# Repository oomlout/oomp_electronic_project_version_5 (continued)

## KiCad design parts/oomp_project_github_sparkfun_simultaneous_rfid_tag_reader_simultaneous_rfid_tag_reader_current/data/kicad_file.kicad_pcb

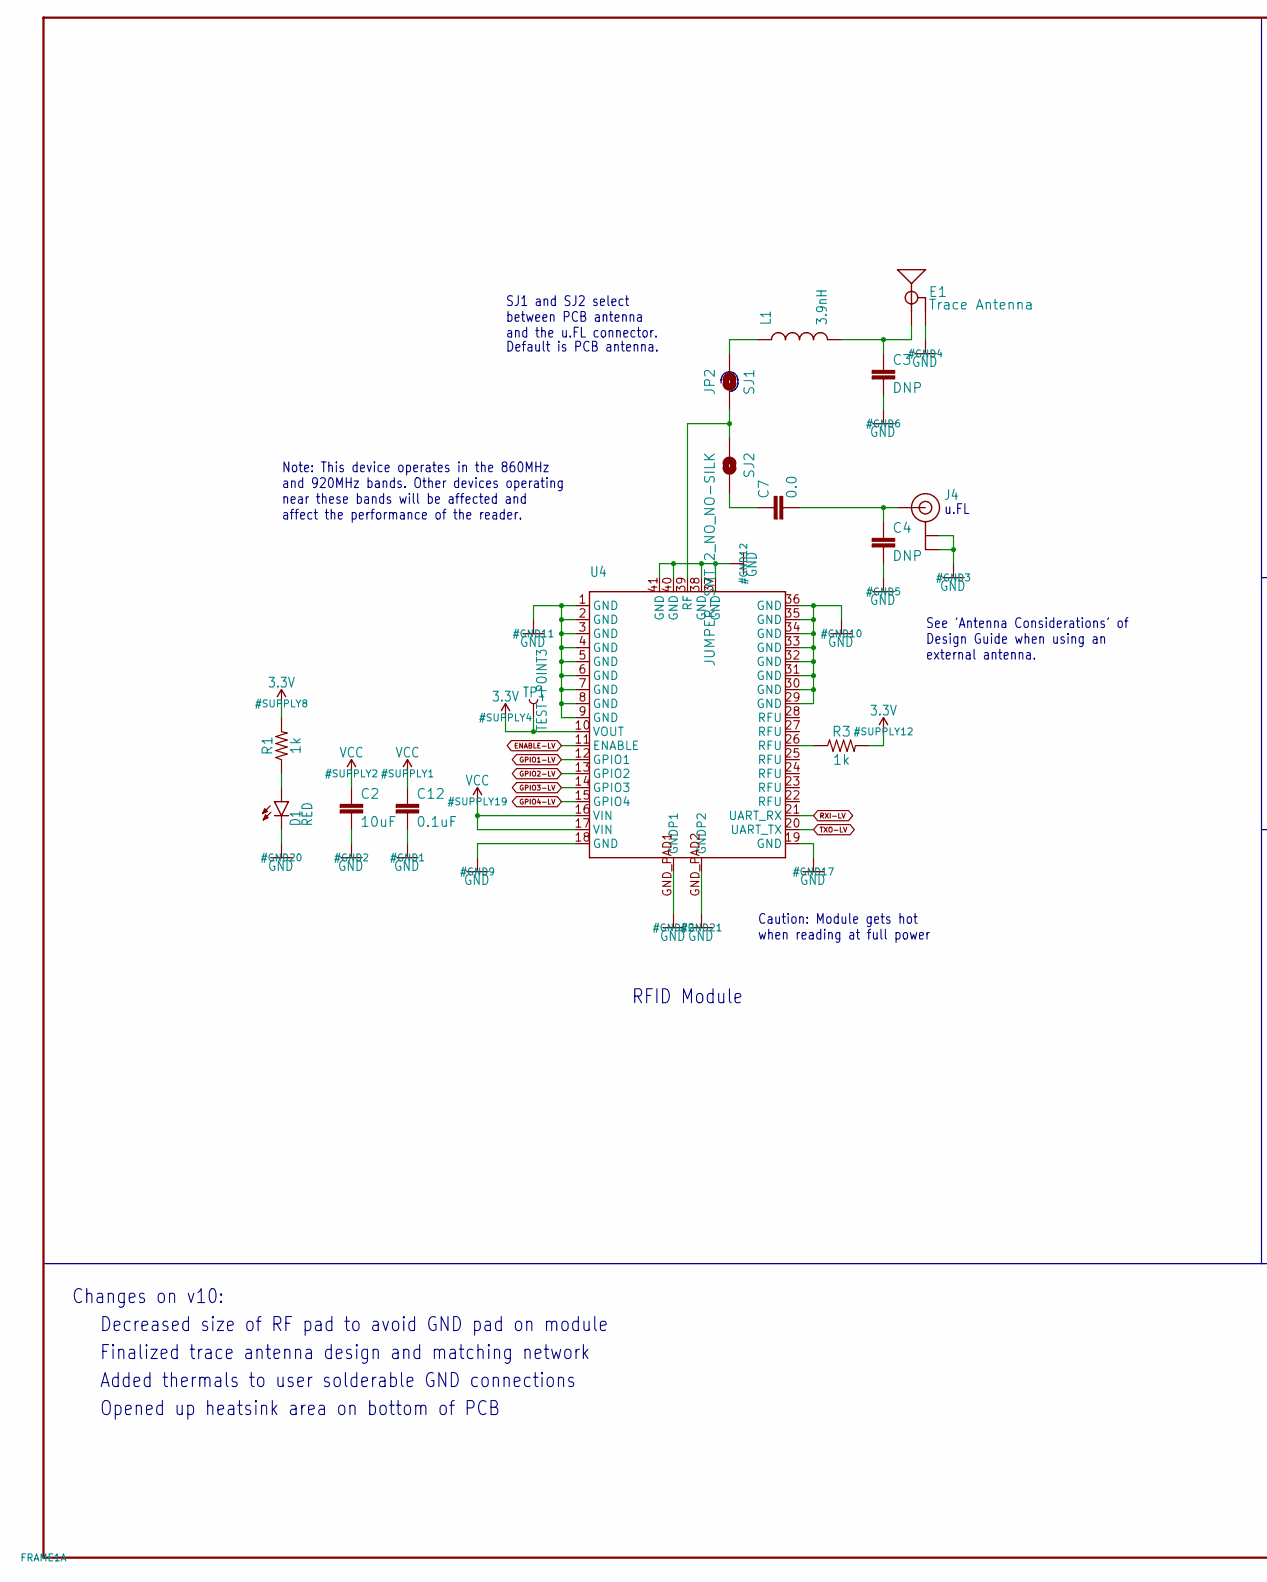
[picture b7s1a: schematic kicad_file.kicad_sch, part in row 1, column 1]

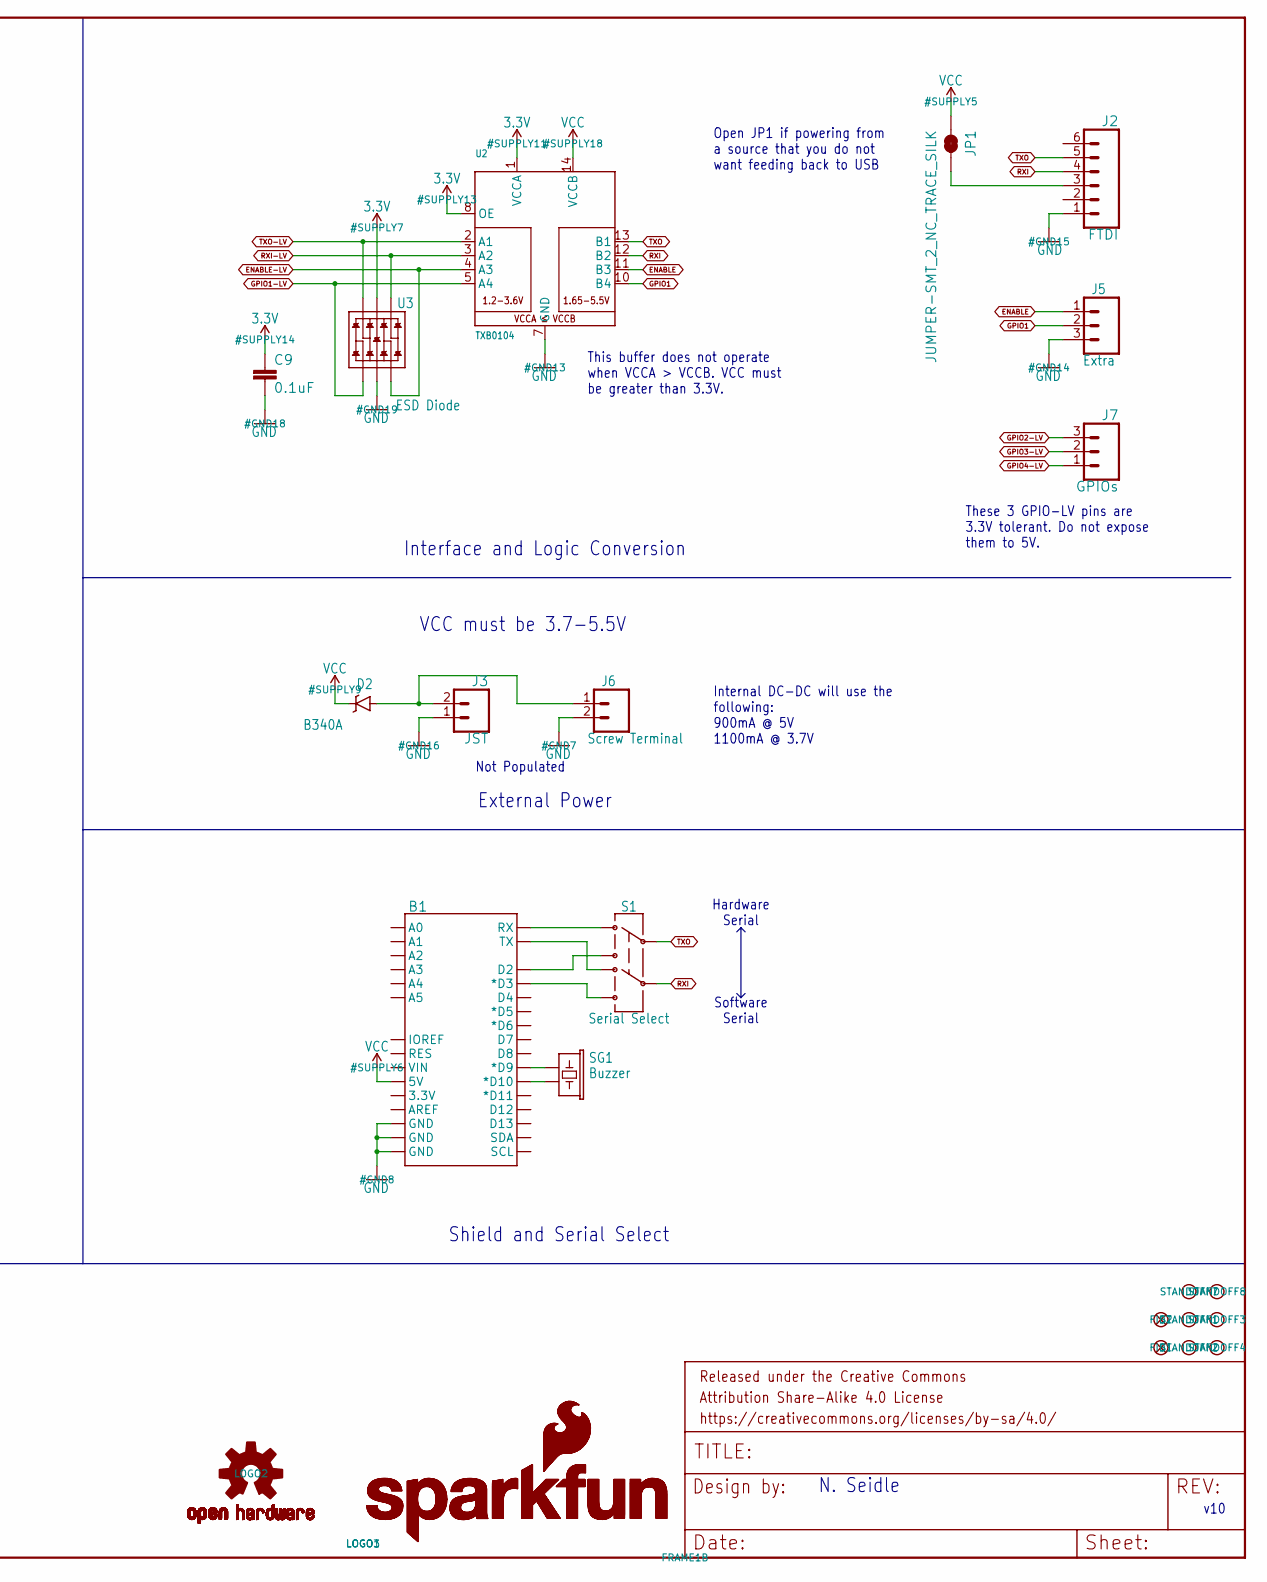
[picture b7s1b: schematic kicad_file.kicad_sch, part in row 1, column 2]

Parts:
B1: ARDUINO_UNO_SHIELD; UNO_R3_SHIELD
C2: 10uF; 0805
C3, C4: DNP; 0603
C7: 0.0; 0603
C9, C12: 0.1uF; 0603
D1: RED; LED-0603
D2: B340A; SMA-DIODE
E1: Trace Antenna; 915MHZ_ANTENNA_TRIMBLE
FID1, FID2: FIDUCIAL1X2; FIDUCIAL-1X2
FRAME1: FRAME-LEDGER; CREATIVE_COMMONS
J2: FTDI; 1X06
J3: JST; JST-2-PTH
J4: U.FL
J5: Extra; 1X03
J6: Screw Terminal; SCREWTERMINAL-3.5MM-2
J7: GPIOs; 1X03
JP1: JUMPER-SMT_2_NC_TRACE_SILK; SMT-JUMPER_2_NC_TRACE_SILK
JP2: SJ1; SMT-JUMPER_2_NO_NO-SILK
L1: 3.9nH; 0603
LOGO1, LOGO3: SFE_LOGO_NAME_FLAME.1_INCH; SFE_LOGO_NAME_FLAME_.1
LOGO2: OSHW-LOGOS; OSHW-LOGO-S
R1, R3: 1k; 0603
S1: Serial Select; SWITCH_DPDT_SMD_AYZ0202
SG1: Buzzer; BUZZER-CCV
SJ2: JUMPER-SMT_2_NO_NO-SILK; SMT-JUMPER_2_NO_NO-SILK
STANDOFF1, STANDOFF2, STANDOFF3, STANDOFF4, STANDOFF7, STANDOFF8: STAND-OFF
TP1: TEST-POINT3; PAD.03X.03
U2: TXB0104; SO14
U3: ESD Diode; SOT-23-6
U4: Nano; NANO_MODULE

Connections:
3.3V: C9.1, R1.2, R3.2, TP1.P$1, U2.1 (VCCA), U2.8 (OE), U3.5 (VCC), U4.10 (VOUT)
ANT3: JP2.1, SJ2.1, U4.39 (RF)
ENABLE: J5.1, U2.11 (B3)
ENABLE-LV: U2.4 (A3), U3.3 (IO2), U4.11 (ENABLE)
GND: B1.GND@0 (GND), B1.GND@1 (GND), B1.GND@2 (GND), C2.2, C3.2, C4.2, C9.2, C12.2, D1.C, E1.GND@1 (GND), E1.GND@2 (GND), E1.GND@3 (GND), J2.1, J3.1, J4.P$1 (GND), J4.P$2 (GND), J5.3, J6.2, U2.7 (GND), U3.2 (VSS), U4.1 (GND), U4.2 (GND), U4.3 (GND), U4.4 (GND), U4.5 (GND), U4.6 (GND), U4.7 (GND), U4.8 (GND), U4.9 (GND), U4.18 (GND), U4.19 (GND), U4.29 (GND), U4.30 (GND), U4.31 (GND), U4.32 (GND), U4.33 (GND), U4.34 (GND), U4.35 (GND), U4.36 (GND), U4.37 (GND), U4.38 (GND), U4.40 (GND), U4.41 (GND), U4.GND_PAD1 (GNDP1), U4.GND_PAD2 (GNDP2)
GPIO1: J5.2, U2.10 (B4)
GPIO1-LV: U2.5 (A4), U3.1 (IO1), U4.12 (GPIO1)
GPIO2-LV: J7.3, U4.13 (GPIO2)
GPIO3-LV: J7.2, U4.14 (GPIO3)
GPIO4-LV: J7.1, U4.15 (GPIO4)
unnamed: C3.1, E1.ANT (SIGNAL), L1.2
unnamed: JP2.2, L1.1
unnamed: C7.1, SJ2.2
unnamed: R3.1, U4.26 (RFU)
unnamed: C4.1, C7.2, J4.P$3 (SIGNAL)
unnamed: D1.A, R1.1
unnamed: J2.3, JP1.2
unnamed: B1.RX, S1.1
unnamed: B1.TX, S1.4
unnamed: B1.D9 (*D9), SG1.+ (1)
unnamed: D2.A, J3.2, J6.1
unnamed: B1.D10 (*D10), SG1.- (2)
RXI: J2.4, S1.5, U2.12 (B2)
RXI-LV: U2.3 (A2), U3.4 (IO3), U4.21 (UART_RX)
SOFT-RX: B1.D2, S1.3
SOFT-TX: B1.D3 (*D3), S1.6
TXO: J2.5, S1.2, U2.13 (B1)
TXO-LV: U2.2 (A1), U3.6 (IO4), U4.20 (UART_TX)
VCC: B1.5V, C2.1, C12.1, D2.C, JP1.1, U2.14 (VCCB), U4.16 (VIN), U4.17 (VIN)

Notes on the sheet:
Default is PCB antenna.
This buffer does not operate when VCCA > VCCB. VCC must be greater than 3.3V.
Opened up heatsink area on bottom of PCB
Not Populated
External Power
Open JP1 if powering from a source that you do not want feeding back to USB
Shield and Serial Select
Caution: Module gets hot when reading at full power
Added thermals to user solderable GND connections
v10
RFID Module
Hardware Serial
SJ1 and SJ2 select between PCB antenna and the u.FL connector.
N. Seidle
Note: This device operates in the 860MHz and 920MHz bands. Other devices operating near these bands will be affected and affect the performance of the reader.
Finalized trace antenna design and matching network
u.FL
VCC must be 3.7-5.5V
Decreased size of RF pad to avoid GND pad on module
Internal DC-DC will use the following: 900mA @ 5V 1100mA @ 3.7V
These 3 GPIO-LV pins are 3.3V tolerant. Do not expose them to 5V.
Software Serial
Changes on v10:
Interface and Logic Conversion
See 'Antenna Considerations' of Design Guide when using an external antenna.

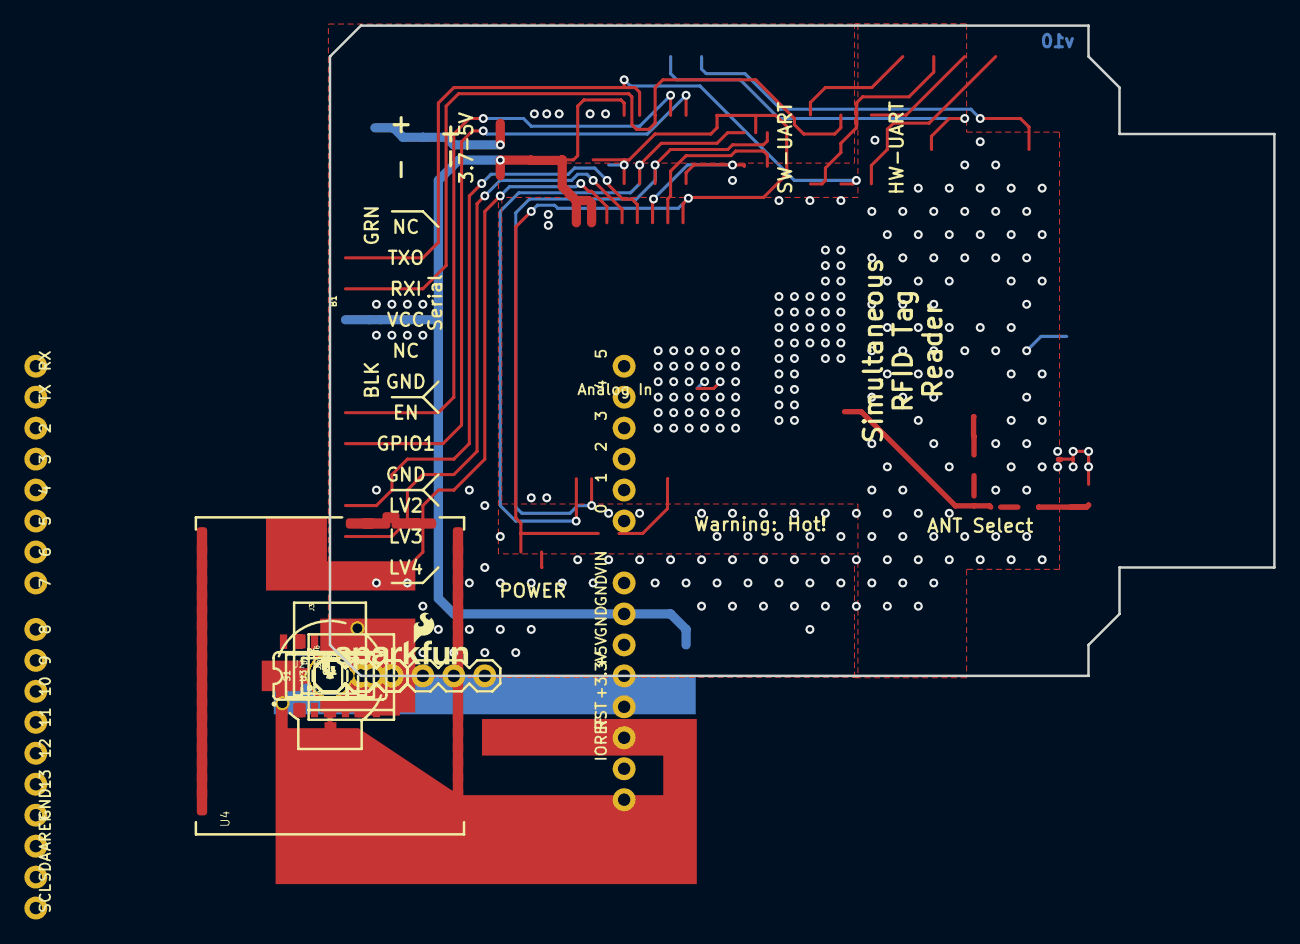
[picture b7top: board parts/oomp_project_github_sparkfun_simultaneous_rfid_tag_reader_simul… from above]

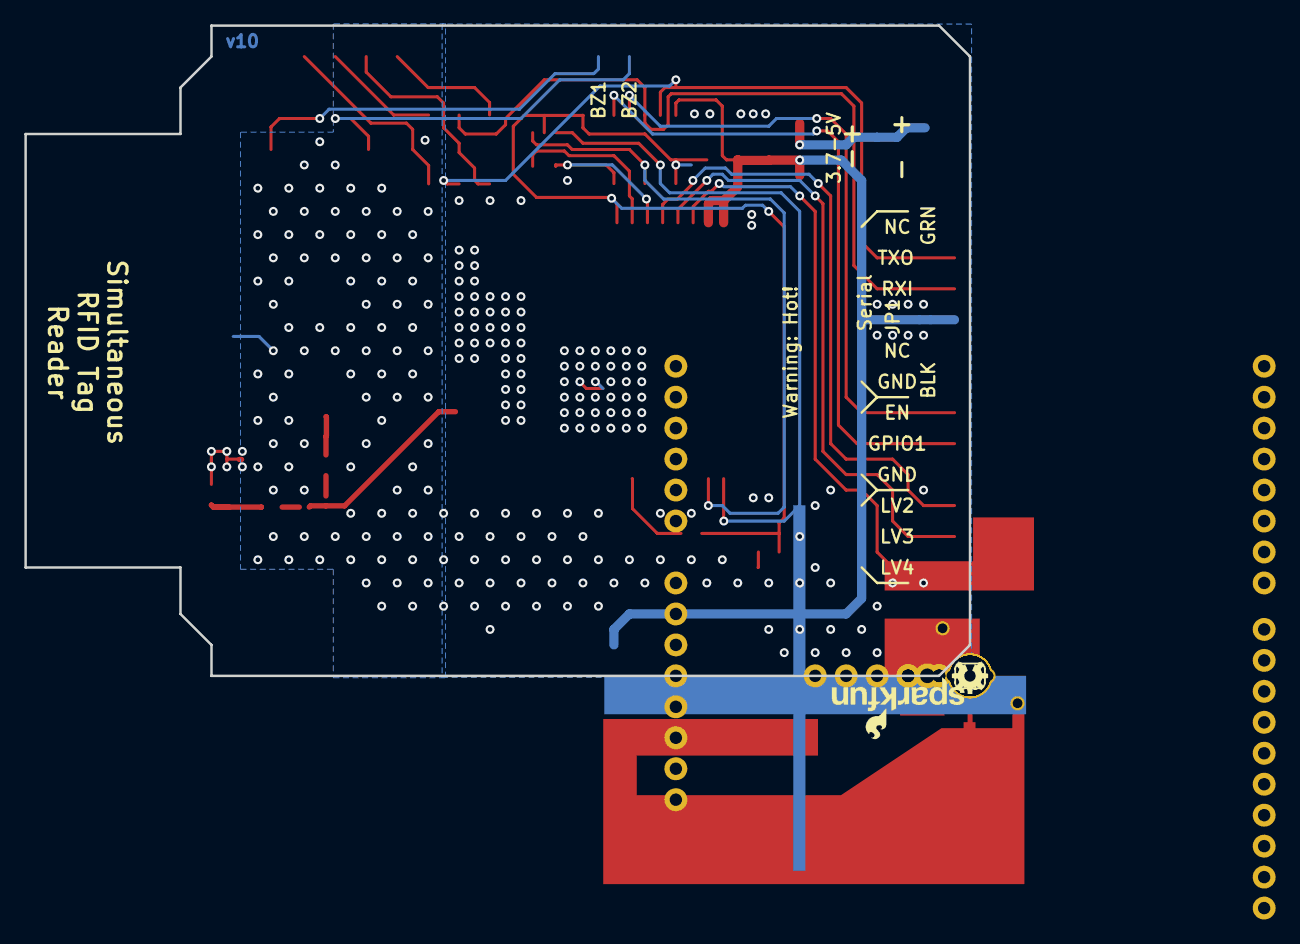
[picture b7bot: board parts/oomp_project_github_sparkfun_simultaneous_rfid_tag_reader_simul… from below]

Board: 2 copper layers, 77.5 x 53.3 mm, 40 parts (4 on the bottom side), 29 nets.

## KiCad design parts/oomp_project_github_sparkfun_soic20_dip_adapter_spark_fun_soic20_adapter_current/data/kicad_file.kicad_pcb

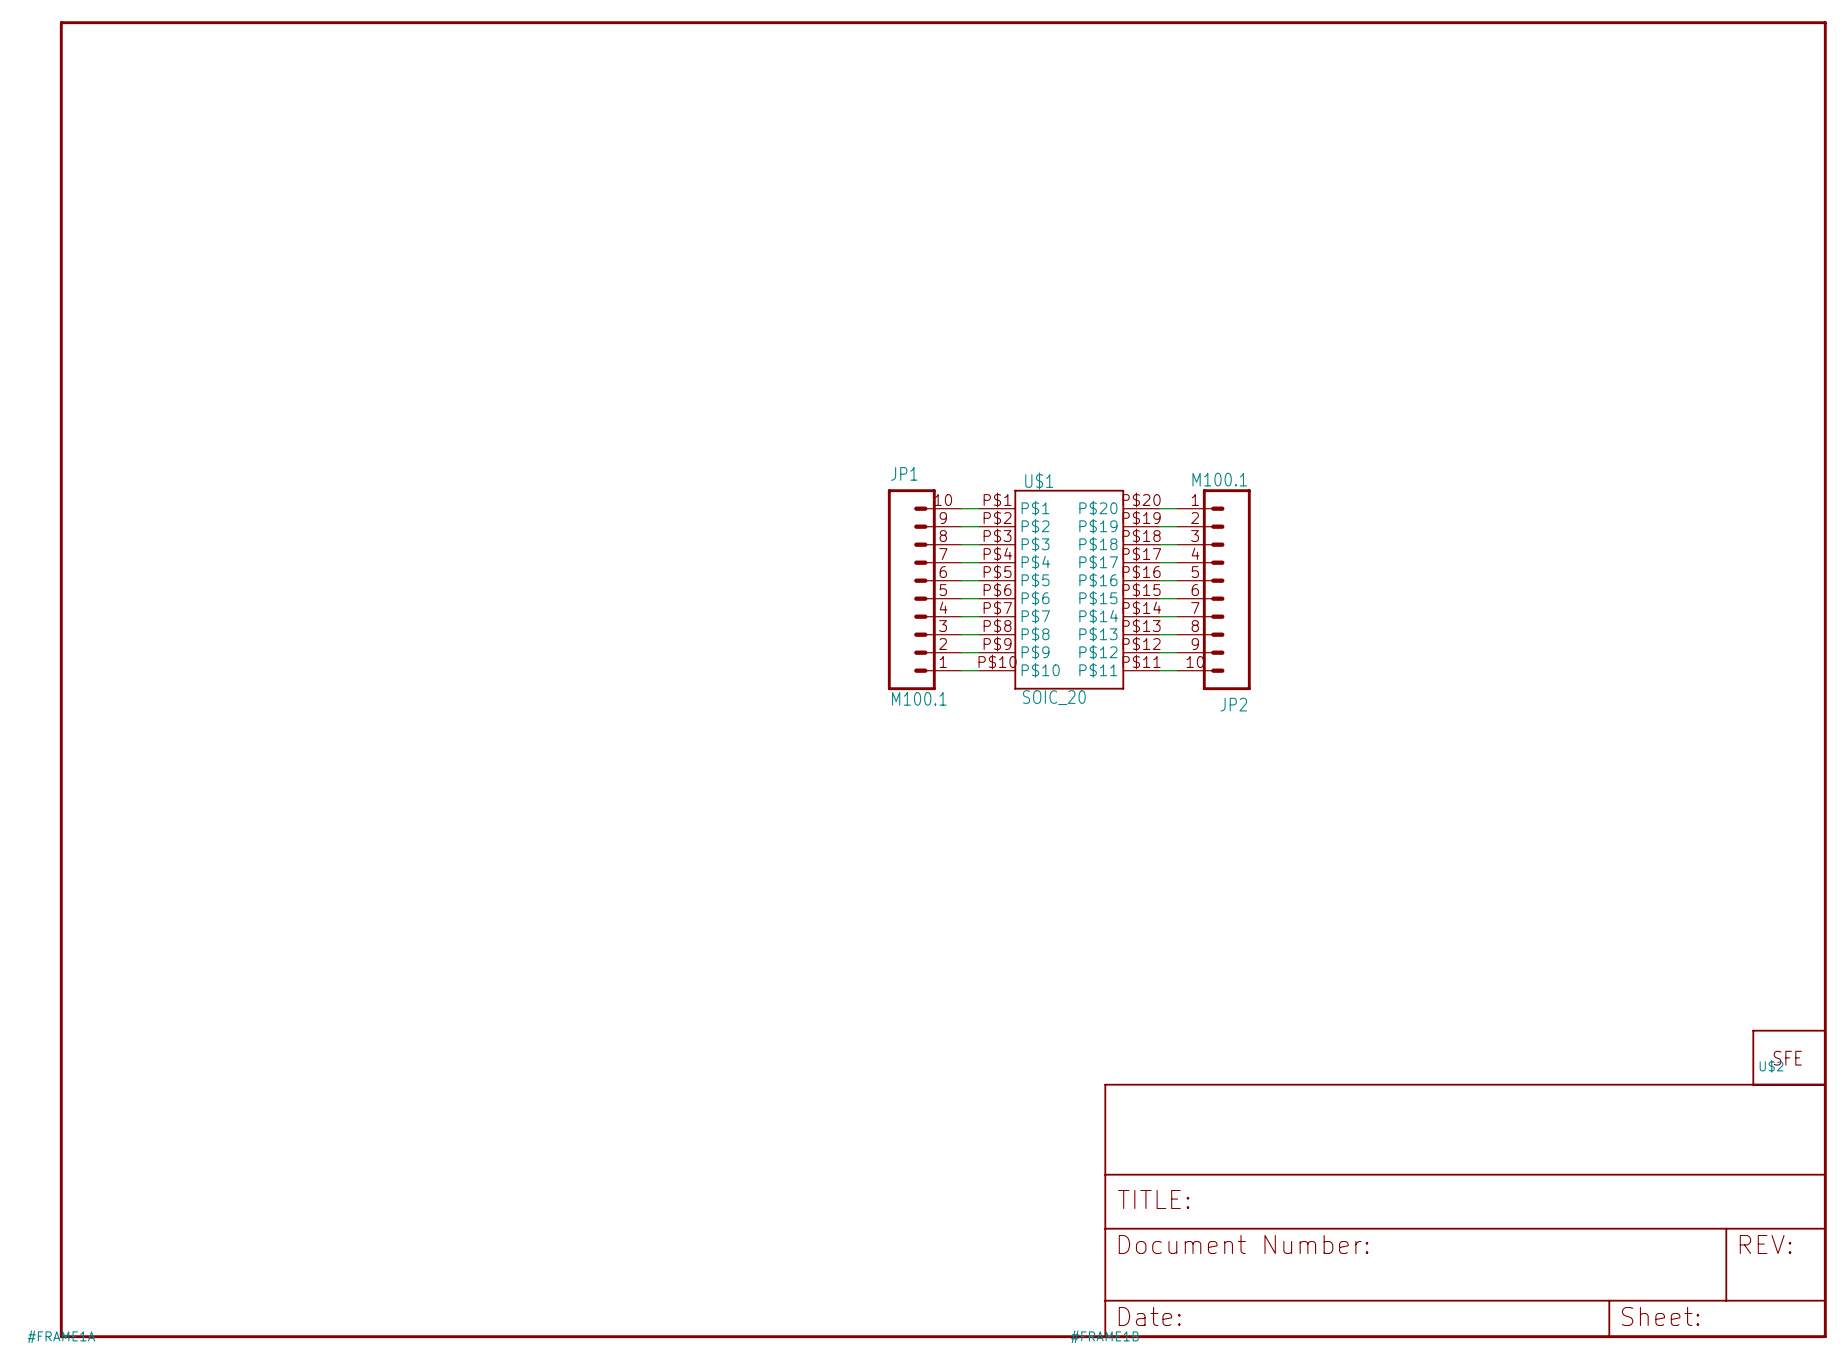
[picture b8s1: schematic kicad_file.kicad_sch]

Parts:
JP1, JP2: M100.1; 1X10
U$1: SOIC_20; SO20W
U$2: LOGO-SFENEW; SFE-NEW-WEBLOGO

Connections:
unnamed: JP1.1, U$1.P$10
unnamed: JP1.2, U$1.P$9
unnamed: JP1.3, U$1.P$8
unnamed: JP1.4, U$1.P$7
unnamed: JP1.5, U$1.P$6
unnamed: JP1.6, U$1.P$5
unnamed: JP1.7, U$1.P$4
unnamed: JP1.8, U$1.P$3
unnamed: JP1.9, U$1.P$2
unnamed: JP1.10, U$1.P$1
unnamed: JP2.1, U$1.P$20
unnamed: JP2.2, U$1.P$19
unnamed: JP2.3, U$1.P$18
unnamed: JP2.4, U$1.P$17
unnamed: JP2.5, U$1.P$16
unnamed: JP2.6, U$1.P$15
unnamed: JP2.7, U$1.P$14
unnamed: JP2.8, U$1.P$13
unnamed: JP2.9, U$1.P$12
unnamed: JP2.10, U$1.P$11

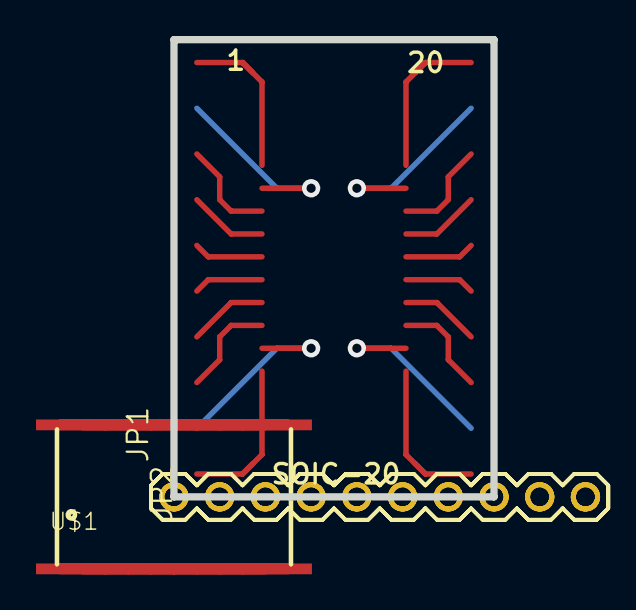
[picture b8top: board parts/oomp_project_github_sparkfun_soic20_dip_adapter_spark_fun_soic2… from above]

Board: 16 copper layers, 17.8 x 25.4 mm, 4 parts (1 on the bottom side), 20 nets.
